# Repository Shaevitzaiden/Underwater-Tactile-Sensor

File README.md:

# Underwater Tactile Sensor
 Soft underwater tactile sensor board

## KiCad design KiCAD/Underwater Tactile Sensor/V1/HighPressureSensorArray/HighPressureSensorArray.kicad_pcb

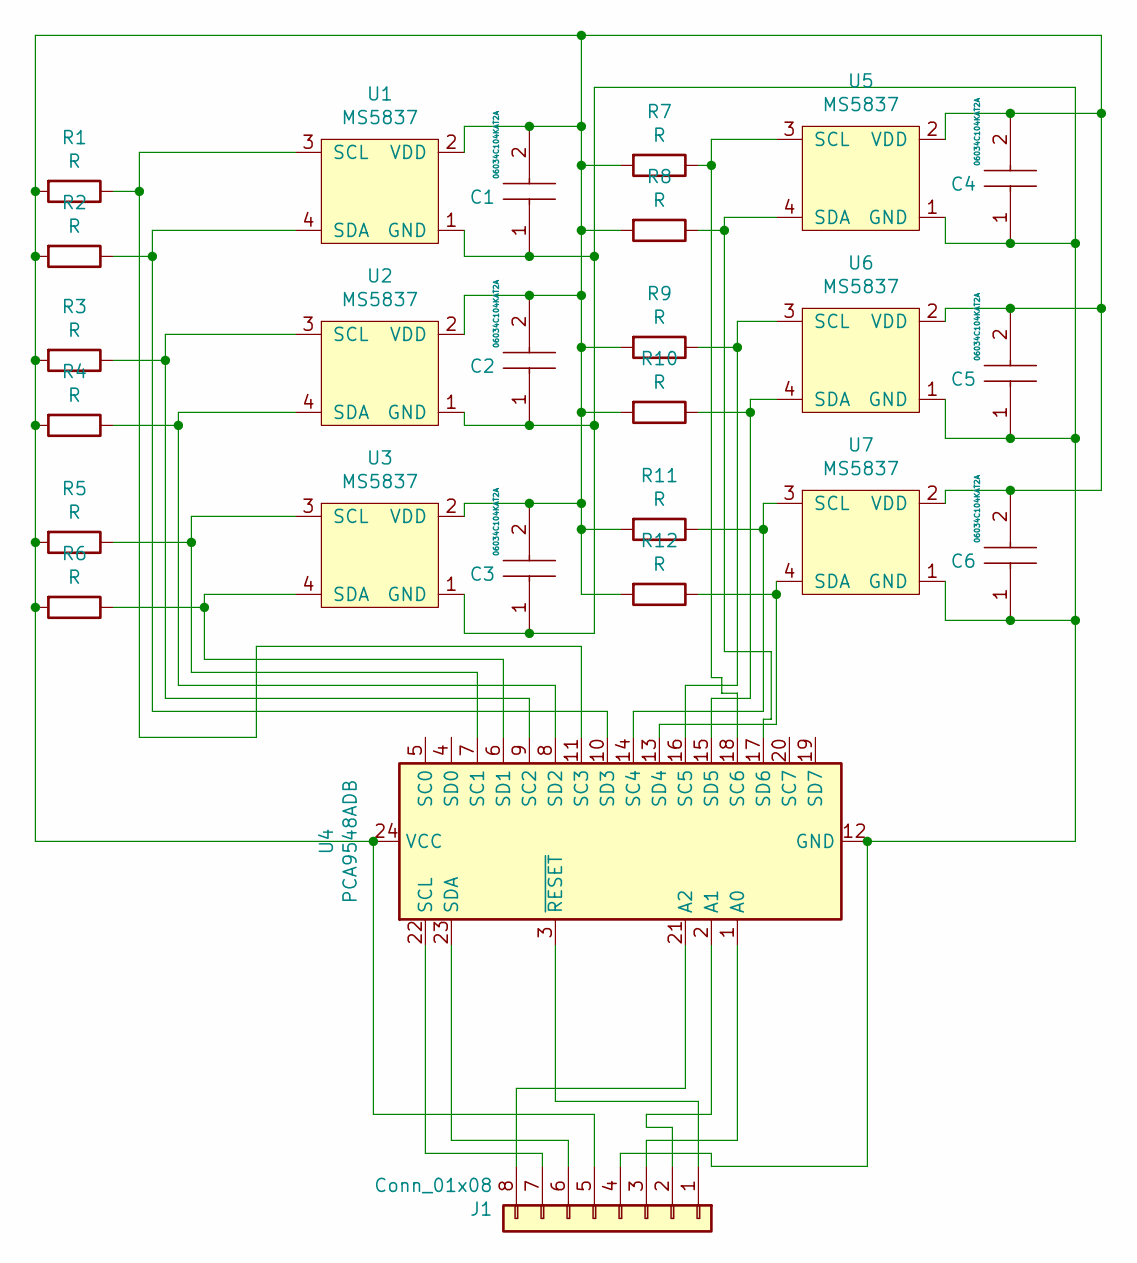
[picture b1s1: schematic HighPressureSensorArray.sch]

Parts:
C1, C2, C3, C4, C5, C6: 06034C104KAT2A; CAPC1608X90N; Mouser Part Number 581-06034C104KAT2A
J1: Conn_01x08; PinHeader_1x08_P2.54mm_Horizontal
R1, R2, R3, R4, R5, R6, R7, R8, R9, R10, R11, R12: R; R_Axial_DIN0207_L6.3mm_D2.5mm_P7.62mm_Horizontal
U1, U2, U3, U5, U6, U7: MS5837; MS5837-30B
U4: PCA9548ADB; SSOP-24_5.3x8.2mm_P0.65mm

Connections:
unnamed: C1.1, C2.1, C3.1, C4.1, C5.1, C6.1, J1.4, U1.1 (GND), U2.1 (GND), U3.1 (GND), U4.12 (GND), U5.1 (GND), U6.1 (GND), U7.1 (GND)
unnamed: C1.2, C2.2, C3.2, C4.2, C5.2, C6.2, J1.5, R1.2, R2.2, R3.2, R4.2, R5.2, R6.2, R7.2, R8.2, R9.2, R10.2, R11.2, R12.2, U1.2 (VDD), U2.2 (VDD), U3.2 (VDD), U4.24 (VCC), U5.2 (VDD), U6.2 (VDD), U7.2 (VDD)
unnamed: J1.1, U4.3 (~RESET)
unnamed: J1.2, U4.2 (A1)
unnamed: J1.3, U4.1 (A0)
unnamed: J1.6, U4.23 (SDA)
unnamed: J1.7, U4.22 (SCL)
unnamed: J1.8, U4.21 (A2)
unnamed: R1.1, U1.3 (SCL), U4.11 (SC3)
unnamed: R2.1, U1.4 (SDA), U4.10 (SD3)
unnamed: R3.1, U2.3 (SCL), U4.9 (SC2)
unnamed: R4.1, U2.4 (SDA), U4.8 (SD2)
unnamed: R5.1, U3.3 (SCL), U4.7 (SC1)
unnamed: R6.1, U3.4 (SDA), U4.6 (SD1)
unnamed: R7.1, U4.18 (SC6), U5.3 (SCL)
unnamed: R8.1, U4.17 (SD6), U5.4 (SDA)
unnamed: R9.1, U4.16 (SC5), U6.3 (SCL)
unnamed: R10.1, U4.15 (SD5), U6.4 (SDA)
unnamed: R11.1, U4.14 (SC4), U7.3 (SCL)
unnamed: R12.1, U4.13 (SD4), U7.4 (SDA)

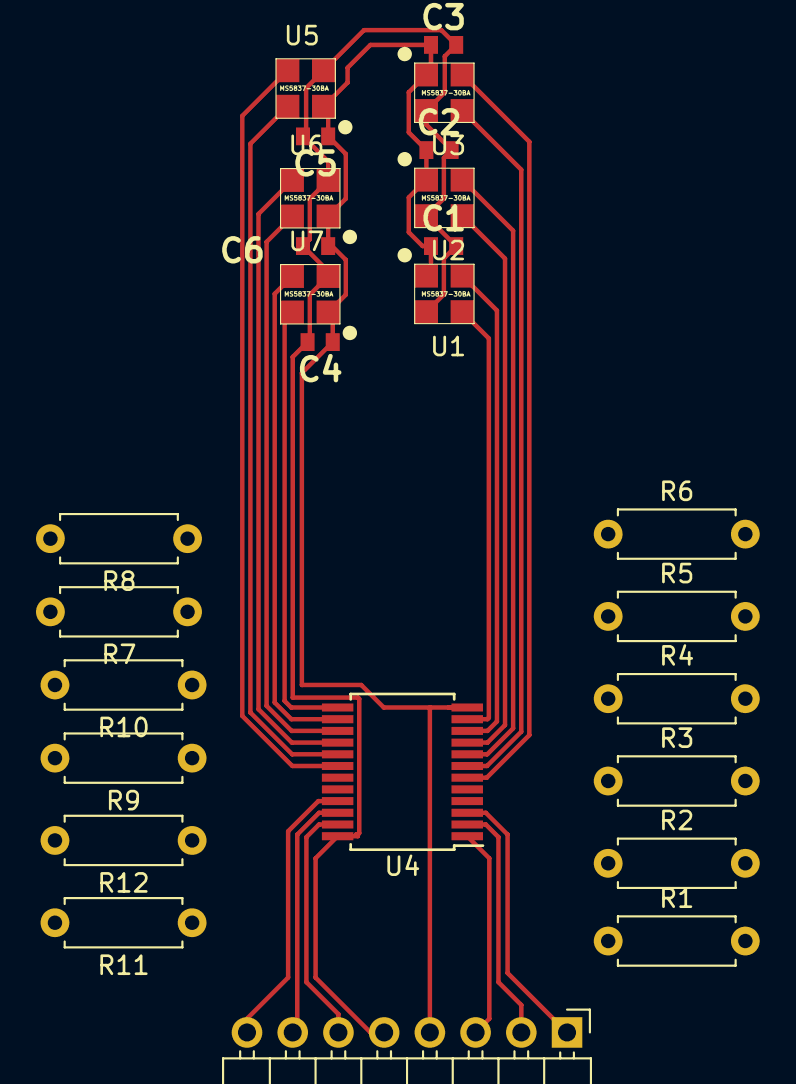
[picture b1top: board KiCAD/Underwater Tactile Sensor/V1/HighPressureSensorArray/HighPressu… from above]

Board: 2 copper layers, 26 parts (0 on the bottom side), 20 nets.

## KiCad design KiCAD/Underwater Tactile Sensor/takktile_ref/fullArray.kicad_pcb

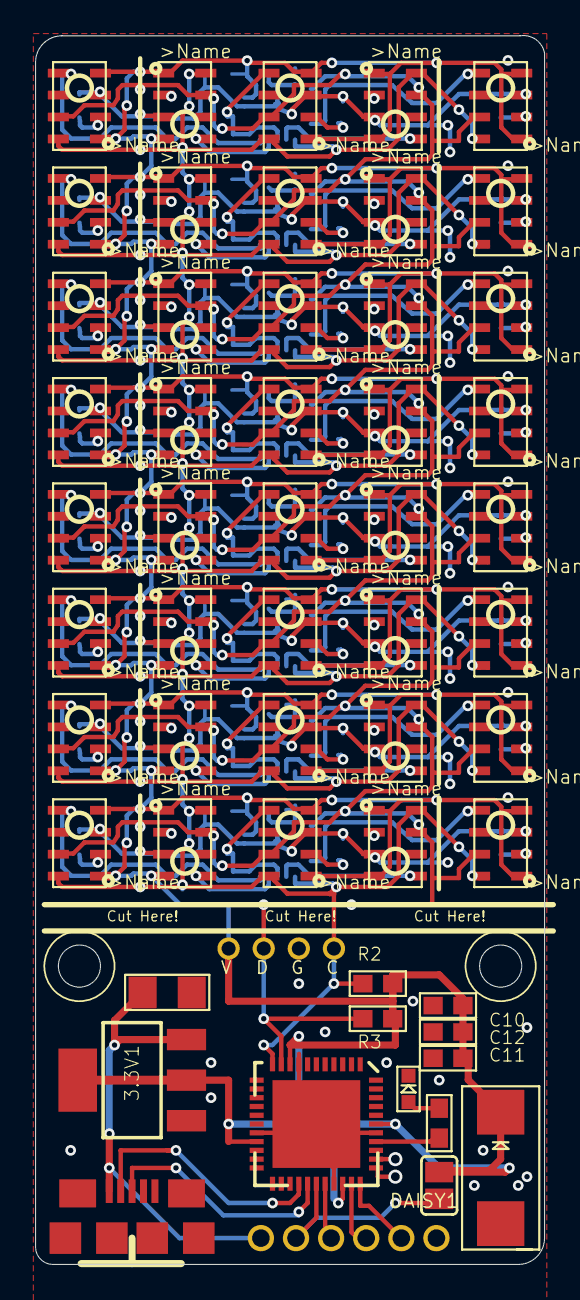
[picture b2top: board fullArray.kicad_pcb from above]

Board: 2 copper layers, 29.0 x 70.0 mm, 117 parts (0 on the bottom side), 93 nets.

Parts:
3.3V1: VREGAP1117; SOT223
@HOLE0, @HOLE1: (no value)
C1, C2, C3, C4, C5, C6, C7, C8, C9, C13, C14, C15, C16, C17, C18, C19, C20, C21, C22, C23, C24, C25, C26, C27, C28, C29, C30, C31, C32, C33, C34, C35, C36, C37, C38, C39, C40, C41, C42, C43, C44, C45, C46, C47, C48, C49, C50, C51: CAP_CERAMIC0402; 0402
C10: 1uF; 0603
C11: .1uF; 0603
C12: .01uF; 0603
C52: 470uF; EIA7343-31_D-R
C53: 10uF; 1206
CN1: USBMICROB; USB-MICROB
DAISY1: HEADER-1X62MM; 1X06_ROUND_2MM
JP1, JP2: HEADER-1X12MM; 1X01_2MM
LED1: LED0603; CHIPLED_0603
R1: 120o; 0603
R2, R3: 4.7K; 0603
SCL1: HEADER-1X12MM; 1X01_2MM
SDA1: HEADER-1X12MM; 1X01_2MM
SJ1: SJ
U$5: LOGO_NONOLITH
UC1, UC2, UC3, UC4, UC5, UC6, UC7, UC8: ATTINY24QFN; QFN20
UNK1, UNK2, UNK3, UNK4, UNK5, UNK6, UNK7, UNK8, UNK9, UNK10, UNK11, UNK12, UNK13, UNK14, UNK15, UNK16, UNK17, UNK18, UNK19, UNK20, UNK21, UNK22, UNK23, UNK24, UNK25, UNK26, UNK27, UNK28, UNK29, UNK30, UNK31, UNK32, UNK33, UNK34, UNK35, UNK36, UNK37, UNK38, UNK39, UNK40: MPL115A; LGA-8
XM1: ATXMEGAXXA4U-MH; QFN-44

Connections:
3.3V: 3.3V1.2, 3.3V1.4, C6.1, C10.2, C11.2, C12.2, C15.1, C21.1, C27.1, C33.1, C39.1, C45.1, C51.1, C52.+, JP2.1, R2.2, R3.2, SJ1.2, UC1.9, UC2.9, UC3.9, UC4.9, UC5.9, UC6.9, UC7.9, UC8.9, UNK1.1, UNK1.4, UNK2.1, UNK2.4, UNK3.1, UNK3.4, UNK4.1, UNK4.4, UNK5.1, UNK5.4, UNK6.1, UNK6.4, UNK7.1, UNK7.4, UNK8.1, UNK8.4, UNK9.1, UNK9.4, UNK10.1, UNK10.4, UNK11.1, UNK11.4, UNK12.1, UNK12.4, UNK13.1, UNK13.4, UNK14.1, UNK14.4, UNK15.1, UNK15.4, UNK16.1, UNK16.4, UNK17.1, UNK17.4, UNK18.1, UNK18.4, UNK19.1, UNK19.4, UNK20.1, UNK20.4, UNK21.1, UNK21.4, UNK22.1, UNK22.4, UNK23.1, UNK23.4, UNK24.1, UNK24.4, UNK25.1, UNK25.4, UNK26.1, UNK26.4, UNK27.1, UNK27.4, UNK28.1, UNK28.4, UNK29.1, UNK29.4, UNK30.1, UNK30.4, UNK31.1, UNK31.4, UNK32.1, UNK32.4, UNK33.1, UNK33.4, UNK34.1, UNK34.4, UNK35.1, UNK35.4, UNK36.1, UNK36.4, UNK37.1, UNK37.4, UNK38.1, UNK38.4, UNK39.1, UNK39.4, UNK40.1, UNK40.4, XM1.9, XM1.19, XM1.31, XM1.39
/fullArray_1/5V: 3.3V1.3, C53.2, CN1.P1, DAISY1.6
/fullArray_1/PE0: DAISY1.5, SJ1.1, XM1.28
/fullArray_1/PE1: DAISY1.4, XM1.29
/fullArray_1/PE2: DAISY1.3, XM1.32
/fullArray_1/PE3: DAISY1.2, XM1.33
/fullArray_1/USB+: CN1.P3, XM1.27
/fullArray_1/USB-: CN1.P2, XM1.26
/fullArray_2/RST01: UC1.5, UNK1.5
/fullArray_2/RST02: UC1.4, UNK2.5
/fullArray_2/RST03: UC1.3, UNK3.5
/fullArray_2/RST04: UC1.2, UNK4.5
/fullArray_2/RST05: UC1.20, UNK5.5
/fullArray_3/RST06: UC2.5, UNK6.5
/fullArray_3/RST07: UC2.4, UNK7.5
/fullArray_3/RST08: UC2.3, UNK8.5
/fullArray_3/RST09: UC2.2, UNK9.5
/fullArray_3/RST10: UC2.20, UNK10.5
/fullArray_4/RST11: UC3.5, UNK11.5
/fullArray_4/RST12: UC3.4, UNK12.5
/fullArray_4/RST13: UC3.3, UNK13.5
/fullArray_4/RST14: UC3.2, UNK14.5
/fullArray_4/RST15: UC3.20, UNK15.5
/fullArray_5/RST16: UC4.5, UNK16.5
/fullArray_5/RST17: UC4.4, UNK17.5
/fullArray_5/RST018: UC4.3, UNK18.5
/fullArray_5/RST19: UC4.2, UNK19.5
/fullArray_5/RST20: UC4.20, UNK20.5
/fullArray_6/RST21: UC5.5, UNK21.5
/fullArray_6/RST22: UC5.4, UNK22.5
/fullArray_6/RST23: UC5.3, UNK23.5
/fullArray_6/RST24: UC5.2, UNK24.5
/fullArray_6/RST25: UC5.20, UNK25.5
/fullArray_7/RST26: UC6.5, UNK26.5
/fullArray_7/RST27: UC6.4, UNK27.5
/fullArray_7/RST28: UC6.3, UNK28.5
/fullArray_7/RST29: UC6.2, UNK29.5
/fullArray_7/RST30: UC6.20, UNK30.5
/fullArray_8/RST31: UC7.5, UNK31.5
/fullArray_8/RST32: UC7.4, UNK32.5
/fullArray_8/RST33: UC7.3, UNK33.5
/fullArray_8/RST34: UC7.2, UNK34.5
/fullArray_8/RST35: UC7.20, UNK35.5
/fullArray_9/RST36: UC8.5, UNK36.5
/fullArray_9/RST37: UC8.4, UNK37.5
/fullArray_9/RST38: UC8.3, UNK38.5
/fullArray_9/RST39: UC8.2, UNK39.5
/fullArray_9/RST40: UC8.20, UNK40.5
GND: 3.3V1.1, C1.2, C2.2, C3.2, C4.2, C5.2, C6.2, C7.2, C8.2, C9.2, C10.1, C11.1, C12.1, C13.2, C14.2, C15.2, C16.2, C17.2, C18.2, C19.2, C20.2, C21.2, C22.2, C23.2, C24.2, C25.2, C26.2, C27.2, C28.2, C29.2, C30.2, C31.2, C32.2, C33.2, C34.2, C35.2, C36.2, C37.2, C38.2, C39.2, C40.2, C41.2, C42.2, C43.2, C44.2, C45.2, C46.2, C47.2, C48.2, C49.2, C50.2, C51.2, C52.-, C53.1, CN1.P5, DAISY1.1, JP1.1, LED1.C, UC1.0, UC1.8, UC1.12, UC1.14, UC1.15, UC2.0, UC2.8, UC2.11, UC2.14, UC2.15, UC3.0, UC3.8, UC3.14, UC3.15, UC4.0, UC4.8, UC4.11, UC4.12, UC4.15, UC5.0, UC5.8, UC5.12, UC5.15, UC6.0, UC6.8, UC6.11, UC6.15, UC7.0, UC7.8, UC7.15, UC8.0, UC8.8, UC8.11, UC8.12, UC8.14, UNK1.3, UNK2.3, UNK3.3, UNK4.3, UNK5.3, UNK6.3, UNK7.3, UNK8.3, UNK9.3, UNK10.3, UNK11.3, UNK12.3, UNK13.3, UNK14.3, UNK15.3, UNK16.3, UNK17.3, UNK18.3, UNK19.3, UNK20.3, UNK21.3, UNK22.3, UNK23.3, UNK24.3, UNK25.3, UNK26.3, UNK27.3, UNK28.3, UNK29.3, UNK30.3, UNK31.3, UNK32.3, UNK33.3, UNK34.3, UNK35.3, UNK36.3, UNK37.3, UNK38.3, UNK39.3, UNK40.3, XM1.8, XM1.18, XM1.30, XM1.38
unnamed: C1.1, UNK1.2
unnamed: C2.1, UNK2.2
unnamed: C3.1, UNK3.2
unnamed: C4.1, UNK4.2
unnamed: C5.1, UNK5.2
unnamed: C7.1, UNK6.2
unnamed: C8.1, UNK7.2
unnamed: C9.1, UNK8.2
unnamed: C13.1, UNK9.2
unnamed: C14.1, UNK10.2
unnamed: C16.1, UNK11.2
unnamed: C17.1, UNK12.2
unnamed: C18.1, UNK13.2
unnamed: C19.1, UNK14.2
unnamed: C20.1, UNK15.2
unnamed: C22.1, UNK16.2
unnamed: C23.1, UNK17.2
unnamed: C24.1, UNK18.2
unnamed: C25.1, UNK19.2
unnamed: C26.1, UNK20.2
unnamed: C28.1, UNK21.2
unnamed: C29.1, UNK22.2
unnamed: C30.1, UNK23.2
unnamed: C31.1, UNK24.2
unnamed: C32.1, UNK25.2
unnamed: C34.1, UNK26.2
unnamed: C35.1, UNK27.2
unnamed: C36.1, UNK28.2
unnamed: C37.1, UNK29.2
unnamed: C38.1, UNK30.2
unnamed: C40.1, UNK31.2
unnamed: C41.1, UNK32.2
unnamed: C42.1, UNK33.2
unnamed: C43.1, UNK34.2
unnamed: C44.1, UNK35.2
unnamed: C46.1, UNK36.2
unnamed: C47.1, UNK37.2
unnamed: C48.1, UNK38.2
unnamed: C49.1, UNK39.2
unnamed: C50.1, UNK40.2
unnamed: LED1.A, R1.2
unnamed: R1.1, XM1.37
SCL: R2.1, SCL1.1, UC1.1, UC2.1, UC3.1, UC4.1, UC5.1, UC6.1, UC7.1, UC8.1, UNK1.8, UNK2.8, UNK3.8, UNK4.8, UNK5.8, UNK6.8, UNK7.8, UNK8.8, UNK9.8, UNK10.8, UNK11.8, UNK12.8, UNK13.8, UNK14.8, UNK15.8, UNK16.8, UNK17.8, UNK18.8, UNK19.8, UNK20.8, UNK21.8, UNK22.8, UNK23.8, UNK24.8, UNK25.8, UNK26.8, UNK27.8, UNK28.8, UNK29.8, UNK30.8, UNK31.8, UNK32.8, UNK33.8, UNK34.8, UNK35.8, UNK36.8, UNK37.8, UNK38.8, UNK39.8, UNK40.8, XM1.11
SDA: R3.1, SDA1.1, UC1.16, UC2.16, UC3.16, UC4.16, UC5.16, UC6.16, UC7.16, UC8.16, UNK1.7, UNK2.7, UNK3.7, UNK4.7, UNK5.7, UNK6.7, UNK7.7, UNK8.7, UNK9.7, UNK10.7, UNK11.7, UNK12.7, UNK13.7, UNK14.7, UNK15.7, UNK16.7, UNK17.7, UNK18.7, UNK19.7, UNK20.7, UNK21.7, UNK22.7, UNK23.7, UNK24.7, UNK25.7, UNK26.7, UNK27.7, UNK28.7, UNK29.7, UNK30.7, UNK31.7, UNK32.7, UNK33.7, UNK34.7, UNK35.7, UNK36.7, UNK37.7, UNK38.7, UNK39.7, UNK40.7, XM1.10

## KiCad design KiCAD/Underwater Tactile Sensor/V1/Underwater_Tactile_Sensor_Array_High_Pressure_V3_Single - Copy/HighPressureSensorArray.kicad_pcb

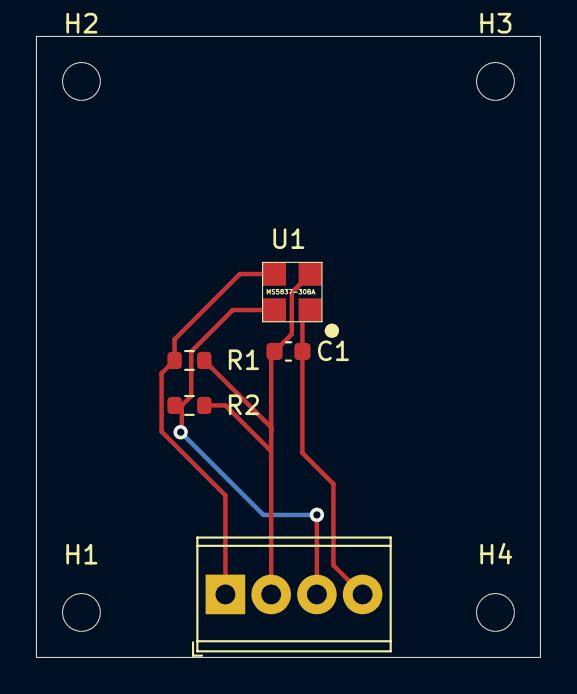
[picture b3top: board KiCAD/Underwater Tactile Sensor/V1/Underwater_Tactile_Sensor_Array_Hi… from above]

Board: 2 copper layers, 28.0 x 34.5 mm, 9 parts (0 on the bottom side), 4 nets.

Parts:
C1: 06034C104KAT2A; C_0603_1608Metric
H1, H2, H3, H4: MountingHole; MountingHole_2.1mm
J1: Screw_Terminal_01x04; TerminalBlock_Phoenix_MPT-0,5-4-2.54_1x04_P2.54mm_Horizontal
R1, R2: R; R_0603_1608Metric
U1: MS5837; MS5837-30B

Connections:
+3V3: C1.2, J1.2, R1.1, R2.1, U1.2
GND: C1.1, J1.4, U1.1
unnamed: J1.1, R1.2, U1.3
unnamed: J1.3, R2.2, U1.4

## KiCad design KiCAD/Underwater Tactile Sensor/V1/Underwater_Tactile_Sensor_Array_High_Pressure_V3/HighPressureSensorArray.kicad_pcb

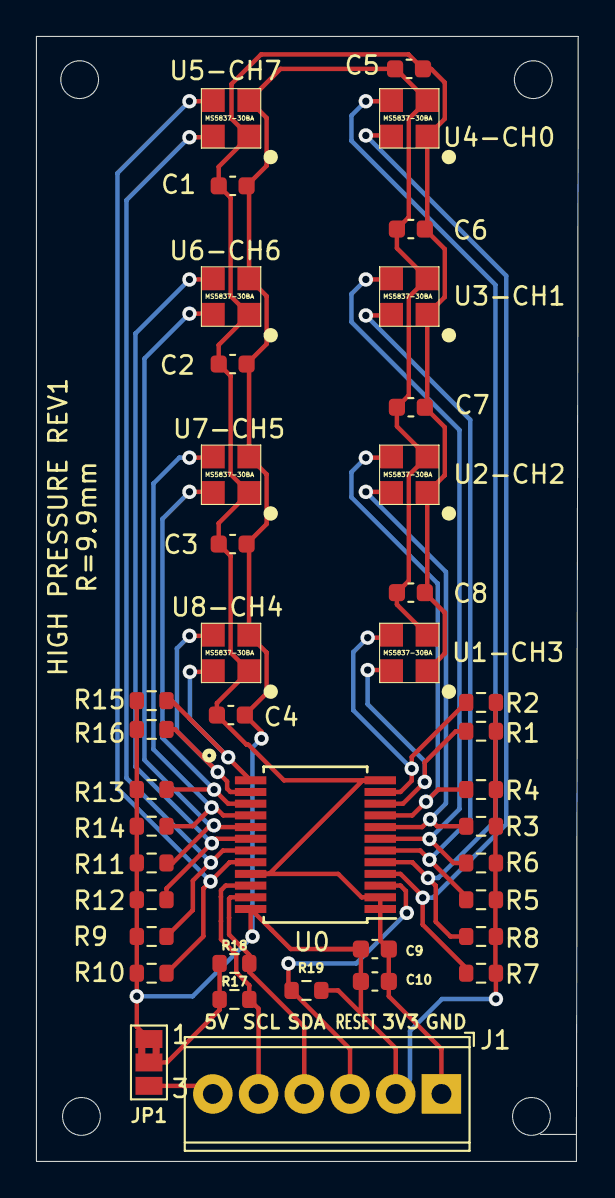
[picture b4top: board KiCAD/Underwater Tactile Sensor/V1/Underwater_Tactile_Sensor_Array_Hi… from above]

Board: 2 copper layers, 30.1 x 62.5 mm, 44 parts (0 on the bottom side), 23 nets.

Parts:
C1, C2, C3, C4, C5, C6, C7, C8: 06034C104KAT2A; C_0603_1608Metric
C9, C10: C; C_0603_1608Metric
H1, H2, H3, H4: MountingHole; MountingHole_2.1mm
J1: Screw_Terminal_01x06; TerminalBlock_Phoenix_MPT-0,5-6-2.54_1x06_P2.54mm_Horizontal
JP1: SolderJumper_3_Bridged12; SolderJumper-3_P1.3mm_Bridged2Bar12_Pad1.0x1.5mm_NumberLabe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
R1, R2, R3, R4, R5, R6, R7, R8, R9, R10, R11, R12, R13, R14, R15, R16, R17, R18, R19: R; R_0603_1608Metric
U0: PCA9548ADB; SSOP-24_5.3x8.2mm_P0.65mm
U1-CH3, U2-CH2, U3-CH1, U4-CH0, U5-CH7, U6-CH6, U7-CH5, U8-CH4: MS5837; MS5837-30B

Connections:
+3V3: C1.2, C2.2, C3.2, C4.2, C5.2, C6.2, C7.2, C8.2, C9.1, C10.1, J1.2, JP1.1, R1.1, R2.1, R3.1, R4.1, R5.1, R6.1, R7.1, R8.1, R9.1, R10.1, R11.1, R12.1, R13.1, R14.1, R15.1, R16.1, R19.1, U0.24, U1-CH3.2, U2-CH2.2, U3-CH1.2, U4-CH0.2, U5-CH7.2, U6-CH6.2, U7-CH5.2, U8-CH4.2
+5V: J1.6, JP1.3
GND: C1.1, C2.1, C3.1, C4.1, C5.1, C6.1, C7.1, C8.1, C9.2, C10.2, J1.1, U0.1, U0.2, U0.12, U0.21, U1-CH3.1, U2-CH2.1, U3-CH1.1, U4-CH0.1, U5-CH7.1, U6-CH6.1, U7-CH5.1, U8-CH4.1
unnamed: J1.3, R19.2, U0.3
unnamed: J1.4, R18.1, U0.23
unnamed: J1.5, R17.1, U0.22
unnamed: JP1.2, R17.2, R18.2
unnamed: R1.2, U0.10, U1-CH3.4
unnamed: R2.2, U0.11, U1-CH3.3
unnamed: R3.2, U0.8, U2-CH2.4
unnamed: R4.2, U0.9, U2-CH2.3
unnamed: R5.2, U0.6, U3-CH1.4
unnamed: R6.2, U0.7, U3-CH1.3
unnamed: R7.2, U0.4, U4-CH0.4
unnamed: R8.2, U0.5, U4-CH0.3
unnamed: R9.2, U0.19, U5-CH7.4
unnamed: R10.2, U0.20, U5-CH7.3
unnamed: R11.2, U0.17, U6-CH6.4
unnamed: R12.2, U0.18, U6-CH6.3
unnamed: R13.2, U0.15, U7-CH5.4
unnamed: R14.2, U0.16, U7-CH5.3
unnamed: R15.2, U0.13, U8-CH4.4
unnamed: R16.2, U0.14, U8-CH4.3

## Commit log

2022-05-14 added python sensor code
2022-05-14 added arduino code for sensor and test bench
2022-05-15 created heatmap class with increased functionality
2022-05-16 minor improvements
2022-05-23 fully functional serial coms, python and arduino code
2022-05-31 testbed now python controllable
2022-06-06 added in the correct test-bench code (v1)
2022-06-07 added more command functions
    - z-axis stuff
2022-06-14 fixes
2022-06-16 fixed rounding error, changed data save structure
2022-06-27 updated python and ardiuno for temp and ambient pressure
2022-07-01 minor fixes with new hardware
2022-07-05 pain
2022-07-05 Attempt to fix memory and buffer
    Remove restart functionality as it wasn't working. Changed arduino code to try and reduce data string size for memory concerns, also reduced buffer loading as that could be a problem.
2022-07-05 fixed temp storage
2022-07-10 fully functional (albiet badly)
2022-07-19 minor changes
2022-07-19 added timeout
2022-07-20 fixed csv and uncommented wire timeout
2022-07-23 dialing in sampling location for new sensing surface
2022-07-23 Create sensorTestBench-single-barometer.py
    code to run for single barometer testing procedure
2022-07-23 Update Sensor-Test-Bench-v2.ino
    pings 2 sensors now: channels 5 & 7
2022-07-23 Update Sensor-Test-Bench-v2.ino
    remove startup since limit switches are currently not in use
2022-07-25 minor bug fixes
    Arduino and python both working for single tactile sensor and one secondary ambient pressure sensor
2022-07-25 increased movement resolution
2022-07-25 small edits, lots of data
2022-07-25 Create processData.py
    can see some really cool plots of data
2022-07-26 more data
2022-07-26 multi-sample tests and data
2022-07-31 changed arduino to ping barometer 3 instead of 5
2022-08-01 updated sensor surface parameter
2022-08-03 visuals and grid gen changes
2022-08-05 slight edits for testing
2022-08-05 ds10 data
2022-08-09 lots of data and outlier rejection
2022-08-10 Update processData-np.py
    find sensing region radius approximate
2022-08-10 50 psi data
2022-08-10 Update processData-np.py
    better radii of sensing finding with some addition of manual trimming to remove outliers that don't get rejected automatically
2022-08-12 wrote an optimization algorithm
    failed to optimize well
2022-08-24 fixed radius finder problem
    Needed to tile True/False arrays and apply to entire 2darray of vals
2022-09-05 setting up for final testing
2022-09-05 changed file name
2022-09-14 Update Sensor-Test-Bench-v2.ino
    changed to collect from 8 sensors instead of 2
2022-09-14 added silicone to pcb offsets
2022-09-14 Update Sensor-Test-Bench-v2.ino
    updated code for new single sensor boards
2022-09-14 Update sensorTestBench-single-barometer.py
    update python code for new single sensor board --- likely still needs modifications
2022-09-14 Update sensorTestBench-single-barometer.py
    same as previous, probably still needs work, albeit less
2022-09-19 com num change
2022-09-19 com update and sensor test
2022-09-22 single sensor ready for testing
2022-09-22 multi-sensor tested for final
2022-09-29 test data and slight arduino changes
2022-09-29 minor fixes
2022-10-02 data
2022-10-03 single press data
2022-10-03 name change, fix misnaming
2022-10-05 file name change
2022-10-05 new data process + train data
2022-10-11 data for epoxied/casted
2022-10-11 fixed heatmap scaling issue
2022-10-13 added additional outlier filtering
2022-10-20 neural network
2022-10-20 saved a csv
2022-10-21 random 90/10
    best performance has been 2-hidden layer network
2022-10-24 start network comparison
2022-10-26 alll 6 in heatmap
2022-10-29 plot stuff
2022-10-29 found mistake in test branch
2022-10-30 all 6 training models
2022-10-30 plots all 6
    still working on dialing everything in
2022-10-30 plot parameters dialed in
2022-10-30 updated prediction plot
2022-10-31 new data
2022-10-31 name change, graphing improvements
2022-11-02 idk anymore
2023-05-03 start of stuff for proper sensor
2023-05-03 finished tests
    boosted sampling speeds from 12 Hz to 52 Hz. Simulataneous start for conversions does not increase speed and causes some errors in the I2C messaging somehow.
2023-06-23 for karina
    changed name, got rid of random print statements, changed it to operate in loop, provide example on how to print array in serial monitor for testing, and started one-point calibration, but commented 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
2024-06-27 kicad
